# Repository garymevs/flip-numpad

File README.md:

# flip
A numpad that can be assembled upside down (if you want) for a reversed numpad layout

Currently only a FR4 sammich case but there might be a 3D printed case at some point

CAD stuff done in [KiCad](https://www.kicad.org/)

[Firmware](https://github.com/garymevs/vial-qmk)

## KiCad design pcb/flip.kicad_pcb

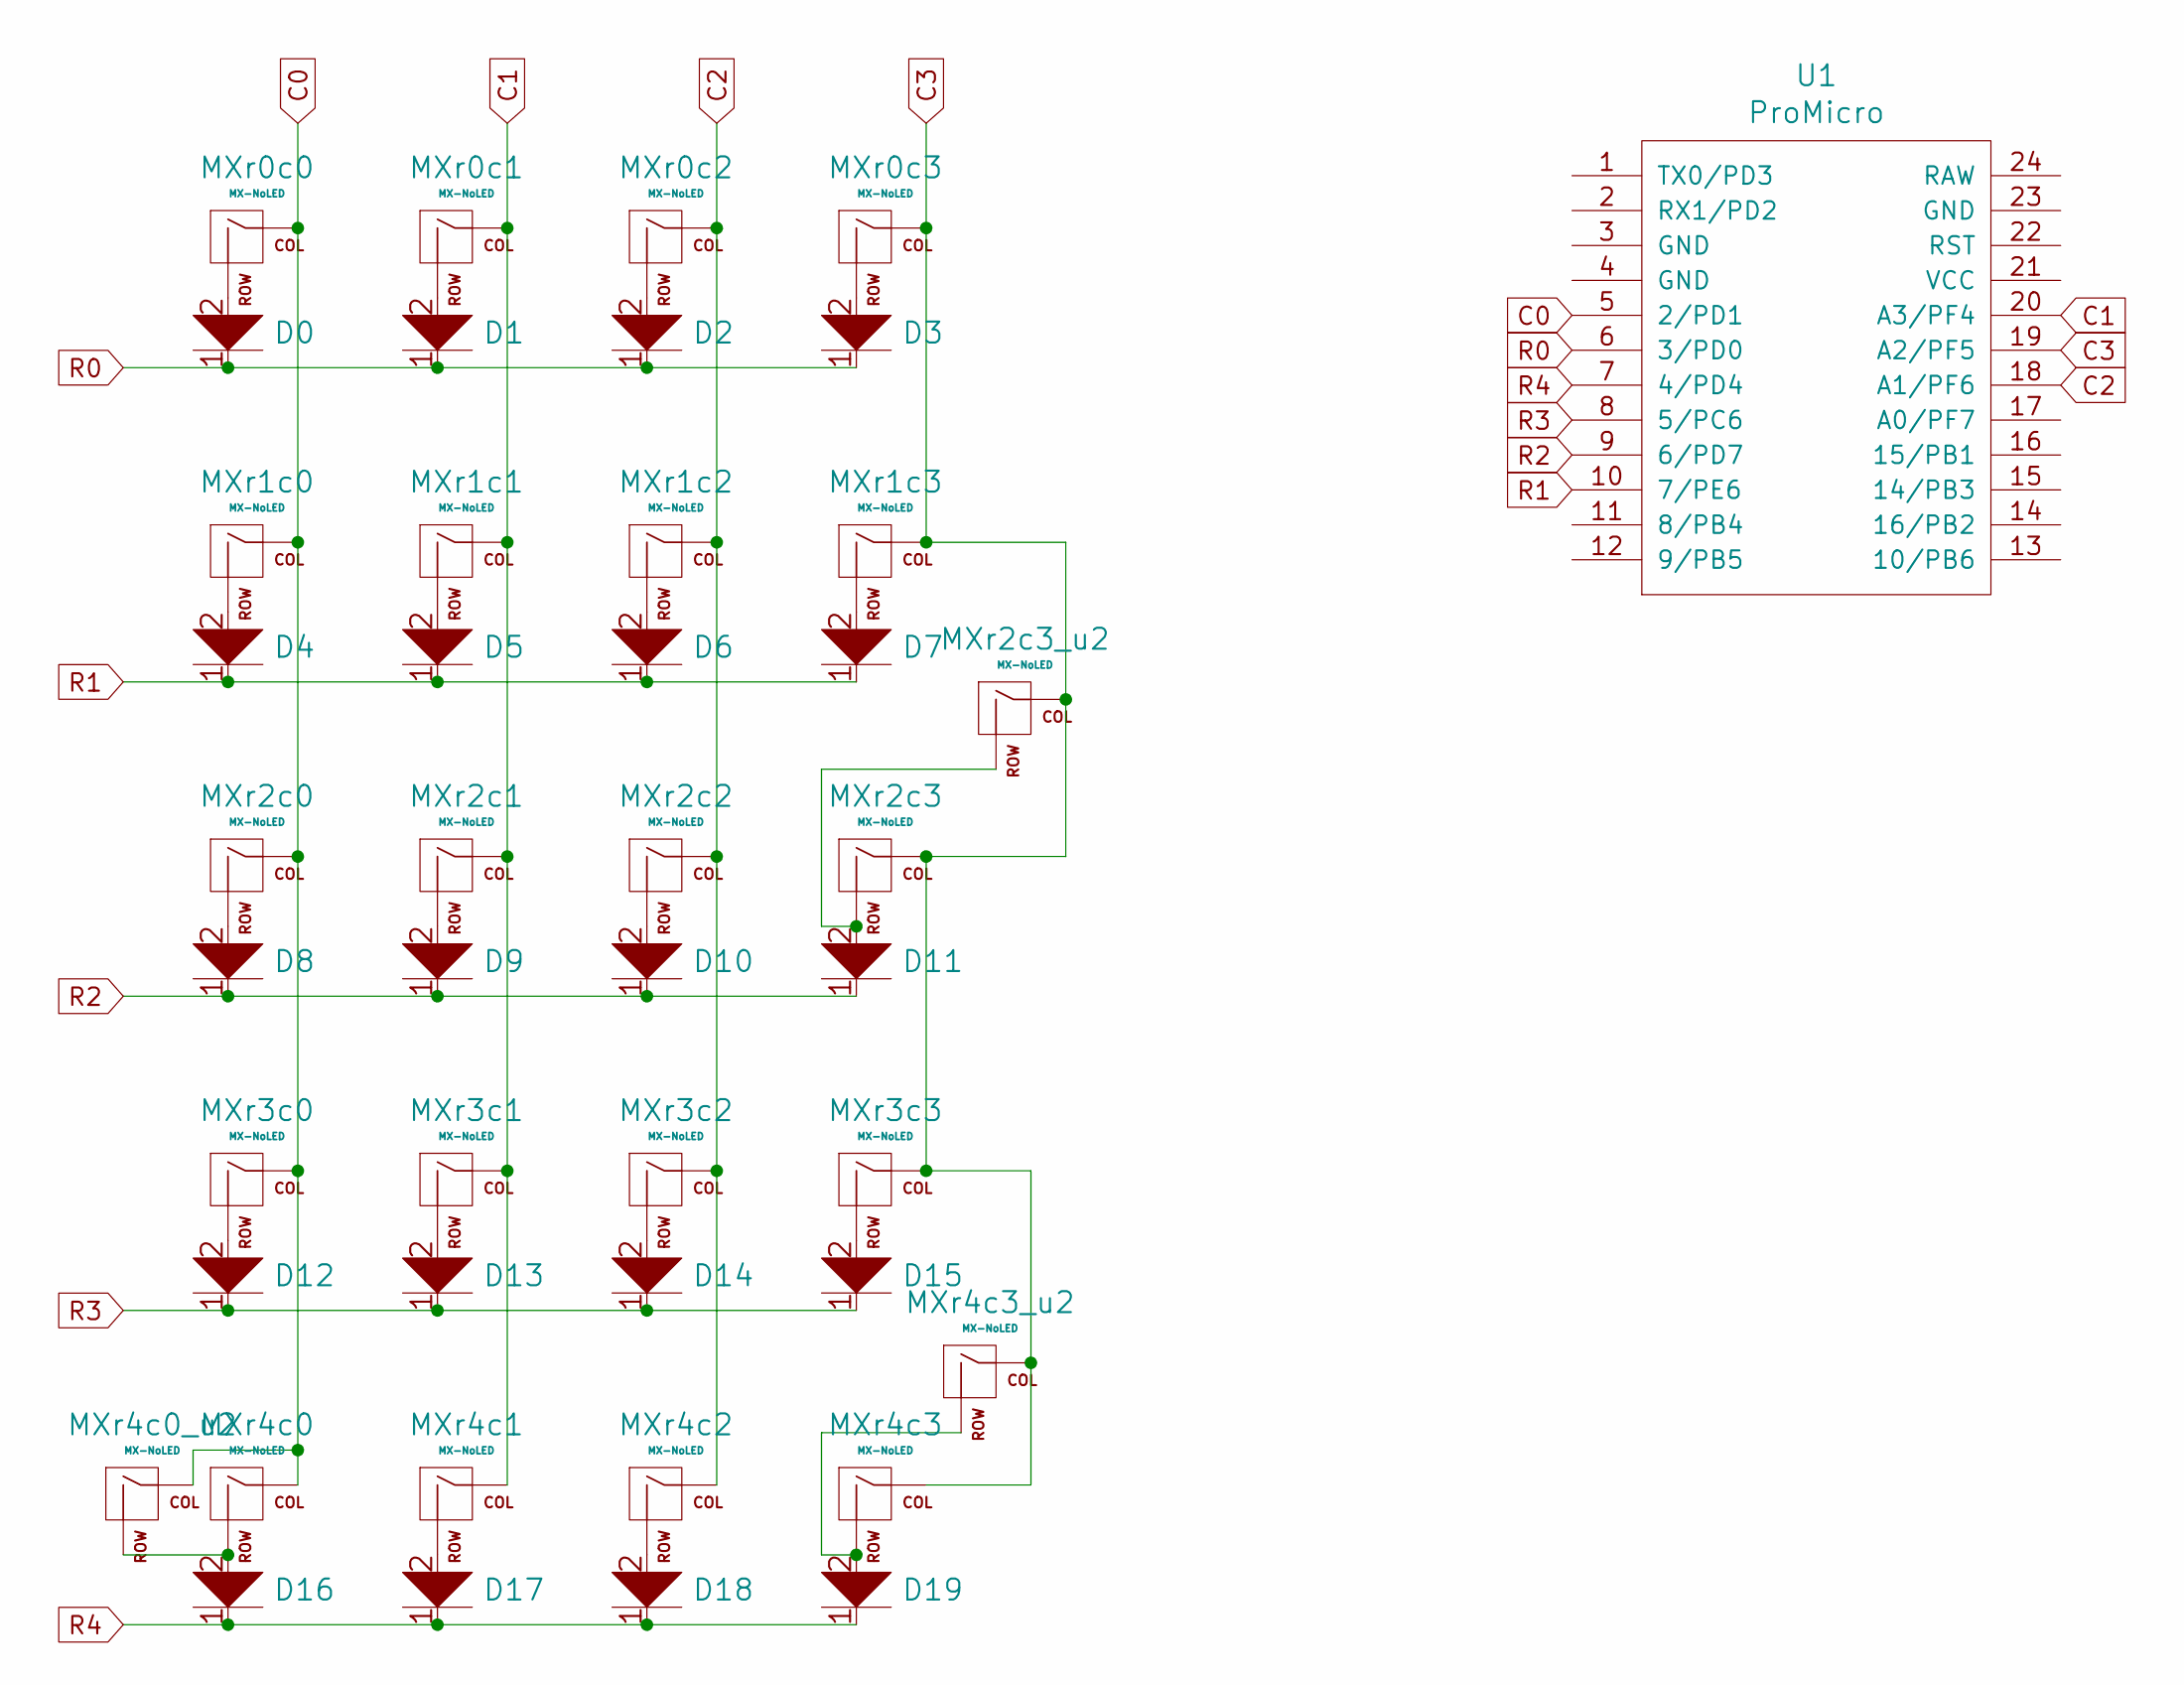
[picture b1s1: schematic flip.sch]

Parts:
D0, D1, D2, D3, D4, D5, D6, D7, D8, D9, D10, D11, D12, D13, D14, D15, D16, D17, D18, D19: D; D_SOD123_axial
MXr0c0, MXr0c1, MXr0c2, MXr0c3, MXr1c0, MXr1c1, MXr1c2, MXr1c3, MXr2c0, MXr2c1, MXr2c2, MXr2c3, MXr3c0, MXr3c1, MXr3c2, MXr3c3, MXr4c0, MXr4c1, MXr4c2, MXr4c3: MX-NoLED; MXOnly-1U-NoLED_combined
MXr2c3_u2, MXr4c0_u2, MXr4c3_u2: MX-NoLED; MXOnly-2U-NoLED_combined
U1: ProMicro; ArduinoProMicro

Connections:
C0: MXr0c0.1 (COL), MXr1c0.1 (COL), MXr2c0.1 (COL), MXr3c0.1 (COL), MXr4c0.1 (COL), MXr4c0_u2.1 (COL), U1.5 (2/PD1)
C1: MXr0c1.1 (COL), MXr1c1.1 (COL), MXr2c1.1 (COL), MXr3c1.1 (COL), MXr4c1.1 (COL), U1.20 (A3/PF4)
C2: MXr0c2.1 (COL), MXr1c2.1 (COL), MXr2c2.1 (COL), MXr3c2.1 (COL), MXr4c2.1 (COL), U1.18 (A1/PF6)
C3: MXr0c3.1 (COL), MXr1c3.1 (COL), MXr2c3.1 (COL), MXr2c3_u2.1 (COL), MXr3c3.1 (COL), MXr4c3.1 (COL), MXr4c3_u2.1 (COL), U1.19 (A2/PF5)
unnamed: D0.2, MXr0c0.2 (ROW)
unnamed: D1.2, MXr0c1.2 (ROW)
unnamed: D2.2, MXr0c2.2 (ROW)
unnamed: D3.2, MXr0c3.2 (ROW)
unnamed: D4.2, MXr1c0.2 (ROW)
unnamed: D5.2, MXr1c1.2 (ROW)
unnamed: D6.2, MXr1c2.2 (ROW)
unnamed: D7.2, MXr1c3.2 (ROW)
unnamed: D8.2, MXr2c0.2 (ROW)
unnamed: D9.2, MXr2c1.2 (ROW)
unnamed: D10.2, MXr2c2.2 (ROW)
unnamed: D11.2, MXr2c3.2 (ROW), MXr2c3_u2.2 (ROW)
unnamed: D12.2, MXr3c0.2 (ROW)
unnamed: D13.2, MXr3c1.2 (ROW)
unnamed: D14.2, MXr3c2.2 (ROW)
unnamed: D15.2, MXr3c3.2 (ROW)
unnamed: D16.2, MXr4c0.2 (ROW), MXr4c0_u2.2 (ROW)
unnamed: D17.2, MXr4c1.2 (ROW)
unnamed: D18.2, MXr4c2.2 (ROW)
unnamed: D19.2, MXr4c3.2 (ROW), MXr4c3_u2.2 (ROW)
R0: D0.1, D1.1, D2.1, D3.1, U1.6 (3/PD0)
R1: D4.1, D5.1, D6.1, D7.1, U1.10 (7/PE6)
R2: D8.1, D9.1, D10.1, D11.1, U1.9 (6/PD7)
R3: D12.1, D13.1, D14.1, D15.1, U1.8 (5/PC6)
R4: D16.1, D17.1, D18.1, D19.1, U1.7 (4/PD4)

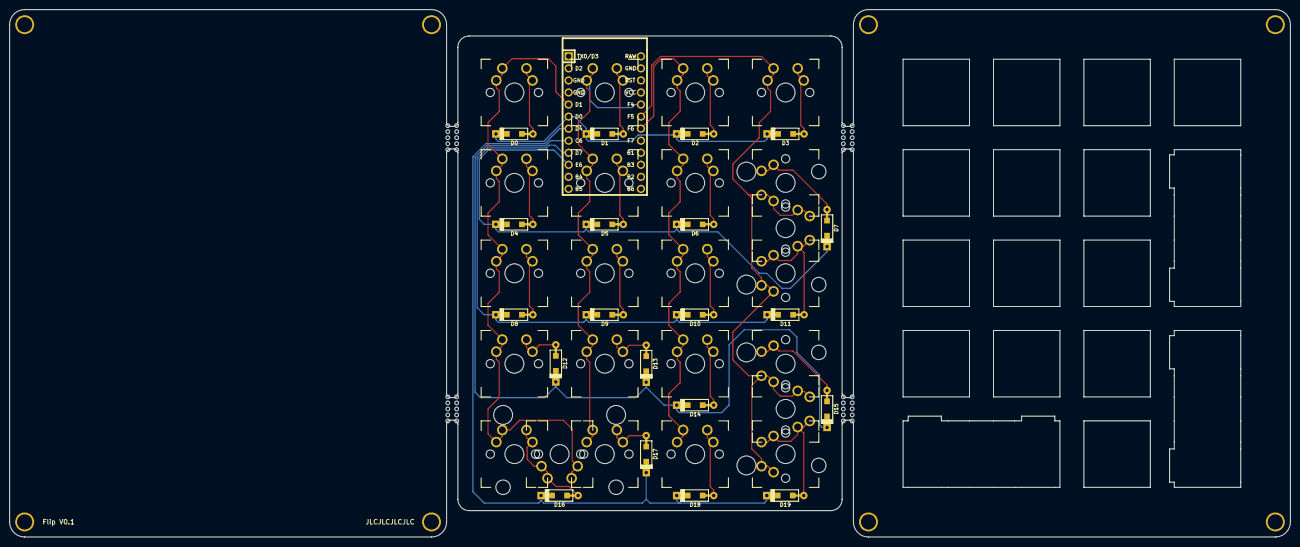
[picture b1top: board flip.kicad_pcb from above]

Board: 2 copper layers, 269.9 x 111.1 mm, 52 parts (0 on the bottom side), 29 nets.

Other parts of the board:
HOLE_M3, HOLE_M3#2, HOLE_M3#3, HOLE_M3#4, HOLE_M3#5, HOLE_M3#6, HOLE_M3#7, HOLE_M3#8: VAL**; HOLE_M3

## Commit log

2021-07-27 Readme stuff
2021-07-29 Create LICENSE
